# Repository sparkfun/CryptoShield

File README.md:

SparkFun CryptoShield
=====================

[*SparkFun CryptoShield (DEV-13183)*](https://www.sparkfun.com/products/13183)

Repository Contents
-------------------

* **/Hardware** - Eagle design files (.brd, .sch)
* **/Production** - Production panel files (.brd)

Documentation
--------------

* **[Hookup Guide](https://learn.sparkfun.com/tutorials/crypto-shield-hookup-guide)** - Basic hookup guide for the CryptoShield.
* **[SparkFun Fritzing repo](https://github.com/sparkfun/Fritzing_Parts)** - Fritzing diagrams for SparkFun products.
* **[SparkFun 3D Model repo](https://github.com/sparkfun/3D_Models)** - 3D models of SparkFun products. 

License Information
-------------------

This product is _**open source**_! 

Please review the LICENSE.md file for license information. 

If you have any questions or concerns on licensing, please contact techsupport@sparkfun.com.

Distributed as-is; no warranty is given.

- Your friends at SparkFun.

_A portion of each sale is given back to Josth Datko for continued development of new and exciting Cryptographic tools._

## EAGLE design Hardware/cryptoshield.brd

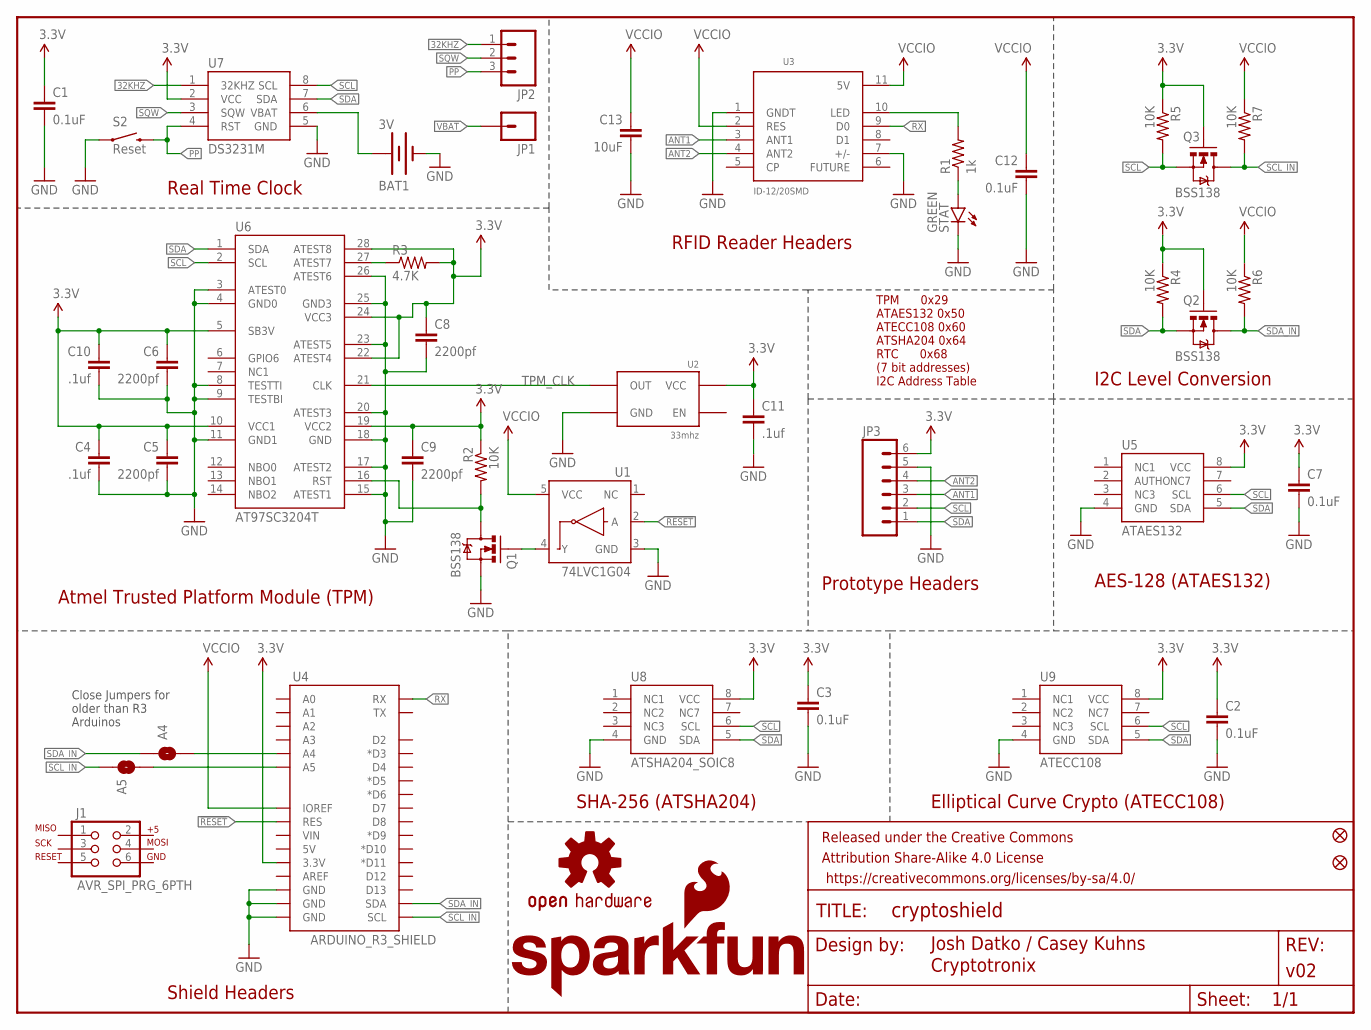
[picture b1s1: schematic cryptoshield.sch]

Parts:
A4, A5: JUMPER-PAD-2-NOYES_SILK; PAD-JUMPER-2-NO_YES_SILK
BAT1: 3V; BATTCON_12MM
C1, C2, C3, C7, C12: 0.1uF; 0603-CAP
C4, C10, C11: .1uf; 0603-CAP
C5, C6, C8, C9: 2200pf; 0603-CAP
C13: 10uF; 1210
FID1, FID2: FIDUCIAL1X2; FIDUCIAL-1X2
FRAME2: FRAME-LETTER; CREATIVE_COMMONS
J1: AVR_SPI_PRG_6PTH; 2X3
JP1: M01PTH; 1X01
JP2: M03PTH; 1X03
JP3: M06NO_SILK_FEMALE_PTH; 1X06_NO_SILK
LOGO2: OSHW-LOGOS; OSHW-LOGO-S
LOGO3: SFE_LOGO_NAME_FLAME.1_INCH; SFE_LOGO_NAME_FLAME_.1
Q1, Q2, Q3: BSS138; SOT23-3
R1: 1k; 0603-RES
R2, R4, R5, R6, R7: 10K; 0603-RES
R3: 4.7K; 0603
S2: Reset; TACTILE-SWITCH-SMD
STAT: GREEN; LED-0603
U1: 74LVC1G04; SOT353
U2: 33mhz; CRYSTAL-OSC-SMD-5X3.2
U3: ID-12/20SMD; ID-12_SMD
U4: ARDUINO_R3_SHIELD; UNO_R3_SHIELD
U5: ATAES132; SOIC8
U6: AT97SC3204T; TSSOP28
U7: DS3231M; SOIC8
U8: ATSHA204_SOIC8; SOIC8
U9: ATECC108; SOIC8

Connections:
3.3V: C1.1, C2.1, C3.1, C4.1, C5.1, C6.1, C7.1, C8.1, C9.1, C10.1, C11.1, JP3.6, Q2.1 (G), Q3.1 (G), R2.1, R3.2, R4.1, R5.1, U2.4 (VCC), U4.3.3V, U5.8 (VCC), U6.5 (SB3V), U6.10 (VCC1), U6.19 (VCC2), U6.22 (ATEST4), U6.24 (VCC3), U6.28 (ATEST8), U7.2 (VCC), U8.8 (VCC), U9.8 (VCC)
32KHZ: JP2.1, U7.1 (32KHZ)
!RESET: U1.2 (A), U4.RES
ANT1: JP3.3, U3.3 (ANT1)
ANT2: JP3.4, U3.4 (ANT2)
GND: BAT1.GND (-), C1.2, C2.2, C3.2, C4.2, C5.2, C6.2, C7.2, C8.2, C9.2, C10.2, C11.2, C12.2, C13.2, JP3.5, Q1.2 (S), S2.1, STAT.C, U1.3 (GND), U2.2 (GND), U3.1 (GNDT), U3.7 (+/-), U4.GND@0 (GND), U4.GND@1 (GND), U4.GND@2 (GND), U5.4 (GND), U6.3 (ATEST0), U6.4 (GND0), U6.8 (TESTTI), U6.9 (TESTBI), U6.11 (GND1), U6.15 (ATEST1), U6.17 (ATEST2), U6.18 (GND), U6.20 (ATEST3), U6.23 (ATEST5), U6.25 (GND3), U6.26 (ATEST6), U7.5 (GND), U8.4 (GND), U9.4 (GND)
unnamed: R1.2, U3.10 (LED)
unnamed: A4.2, U4.A4
unnamed: A5.2, U4.A5
unnamed: R1.1, STAT.A
unnamed: Q1.3 (D), R2.2, U6.16 (RST)
unnamed: R3.1, U6.27 (ATEST7)
unnamed: Q1.1 (G), U1.4 (Y)
PP: JP2.3, S2.3 (2), U7.4 (RST)
RX: U3.9 (D0), U4.RX
SCL: JP3.2, Q3.2 (S), R5.2, U5.6 (SCL), U6.2 (SCL), U7.8 (SCL), U8.6 (SCL), U9.6 (SCL)
SCL_IN: A5.1, Q3.3 (D), R7.2, U4.SCL
SDA: JP3.1, Q2.2 (S), R4.2, U5.5 (SDA), U6.1 (SDA), U7.7 (SDA), U8.5 (SDA), U9.5 (SDA)
SDA_IN: A4.1, Q2.3 (D), R6.2, U4.SDA
SQW: JP2.2, U7.3 (SQW)
TPM_CLK: U2.3 (OUT), U6.21 (CLK)
VBAT: BAT1.PWR@1 (+), JP1.1, U7.6 (VBAT)
VCCIO: C12.1, C13.1, R6.1, R7.1, U1.5 (VCC), U3.2 (RES), U3.11 (5V), U4.IOREF

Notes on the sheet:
Cryptotronix
RFID Reader Headers
I2C Level Conversion
Real Time Clock
Atmel Trusted Platform Module (TPM)
Elliptical Curve Crypto (ATECC108)
SHA-256 (ATSHA204)
Prototype Headers
I2C Address Table
TPM 0x29 ATAES132 0x50 ATECC108 0x60 ATSHA204 0x64 RTC 0x68 (7 bit addresses)
AES-128 (ATAES132)
Shield Headers
Close Jumpers for older than R3 Arduinos

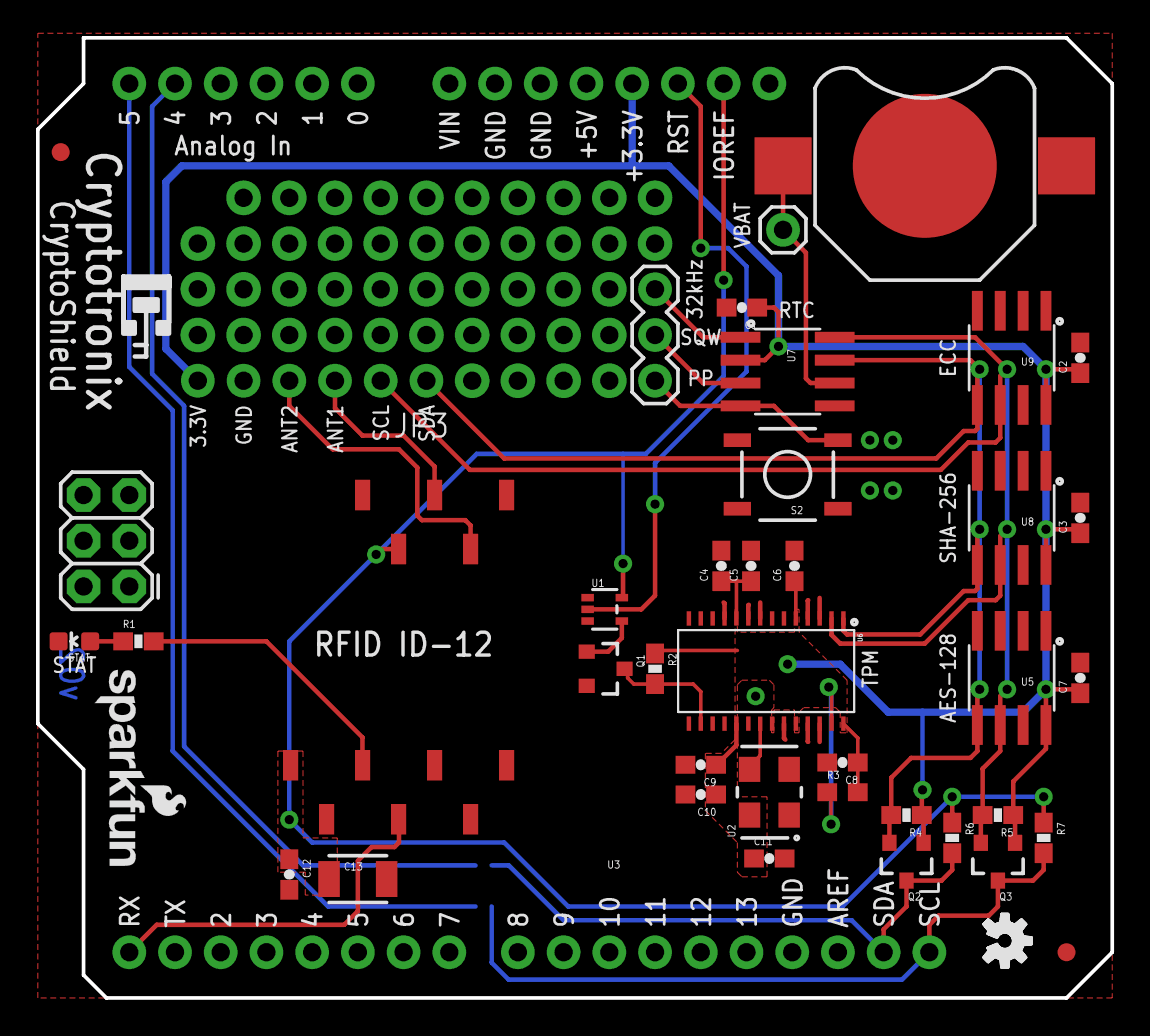
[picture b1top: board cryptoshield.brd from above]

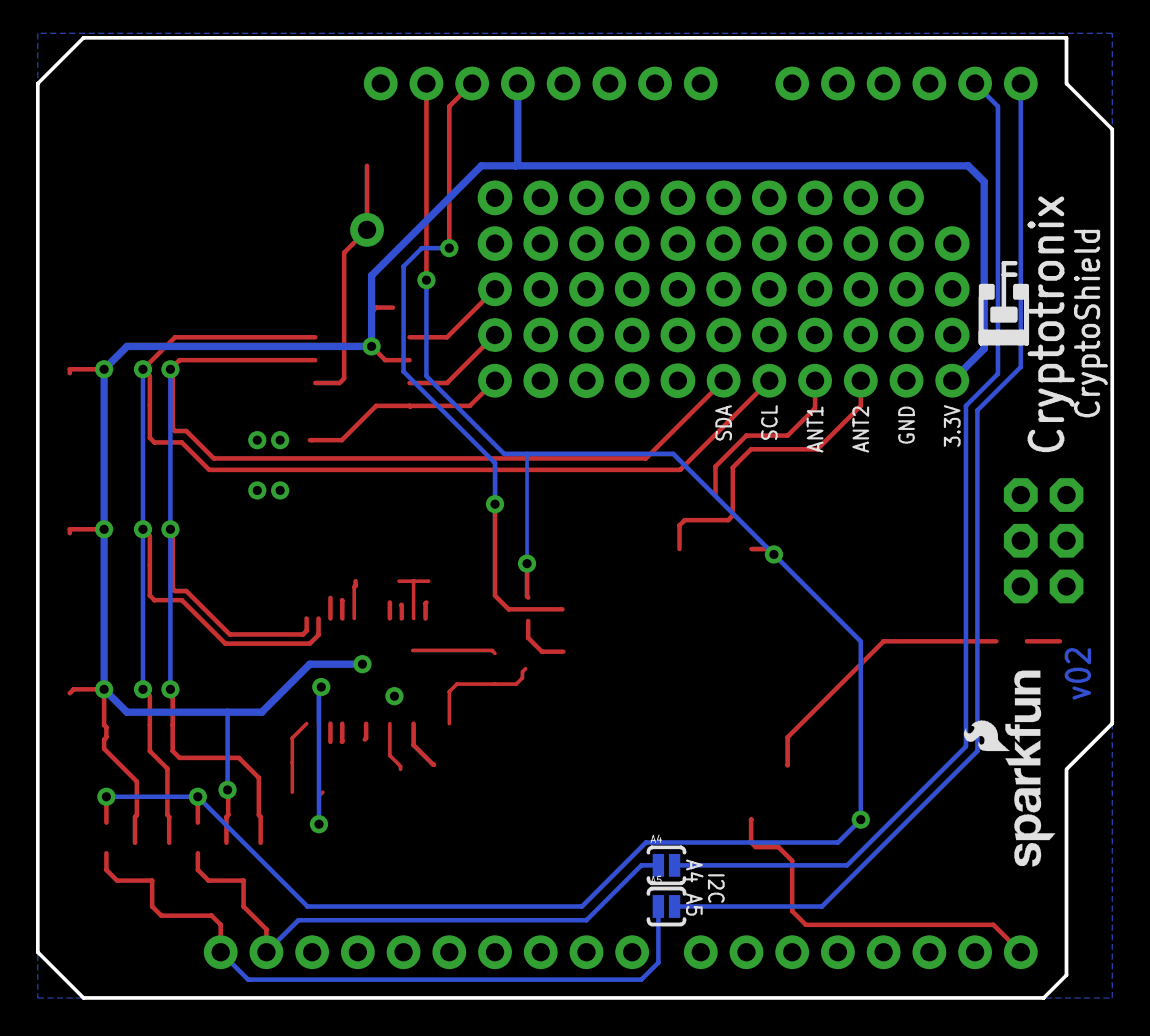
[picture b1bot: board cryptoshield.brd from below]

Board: 2 copper layers, 59.7 x 53.3 mm, 48 parts (3 on the bottom side), 23 nets.

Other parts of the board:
U$3: OSHW-LOGO-S
U$101: SFE_LOGO_NAME_FLAME_.1

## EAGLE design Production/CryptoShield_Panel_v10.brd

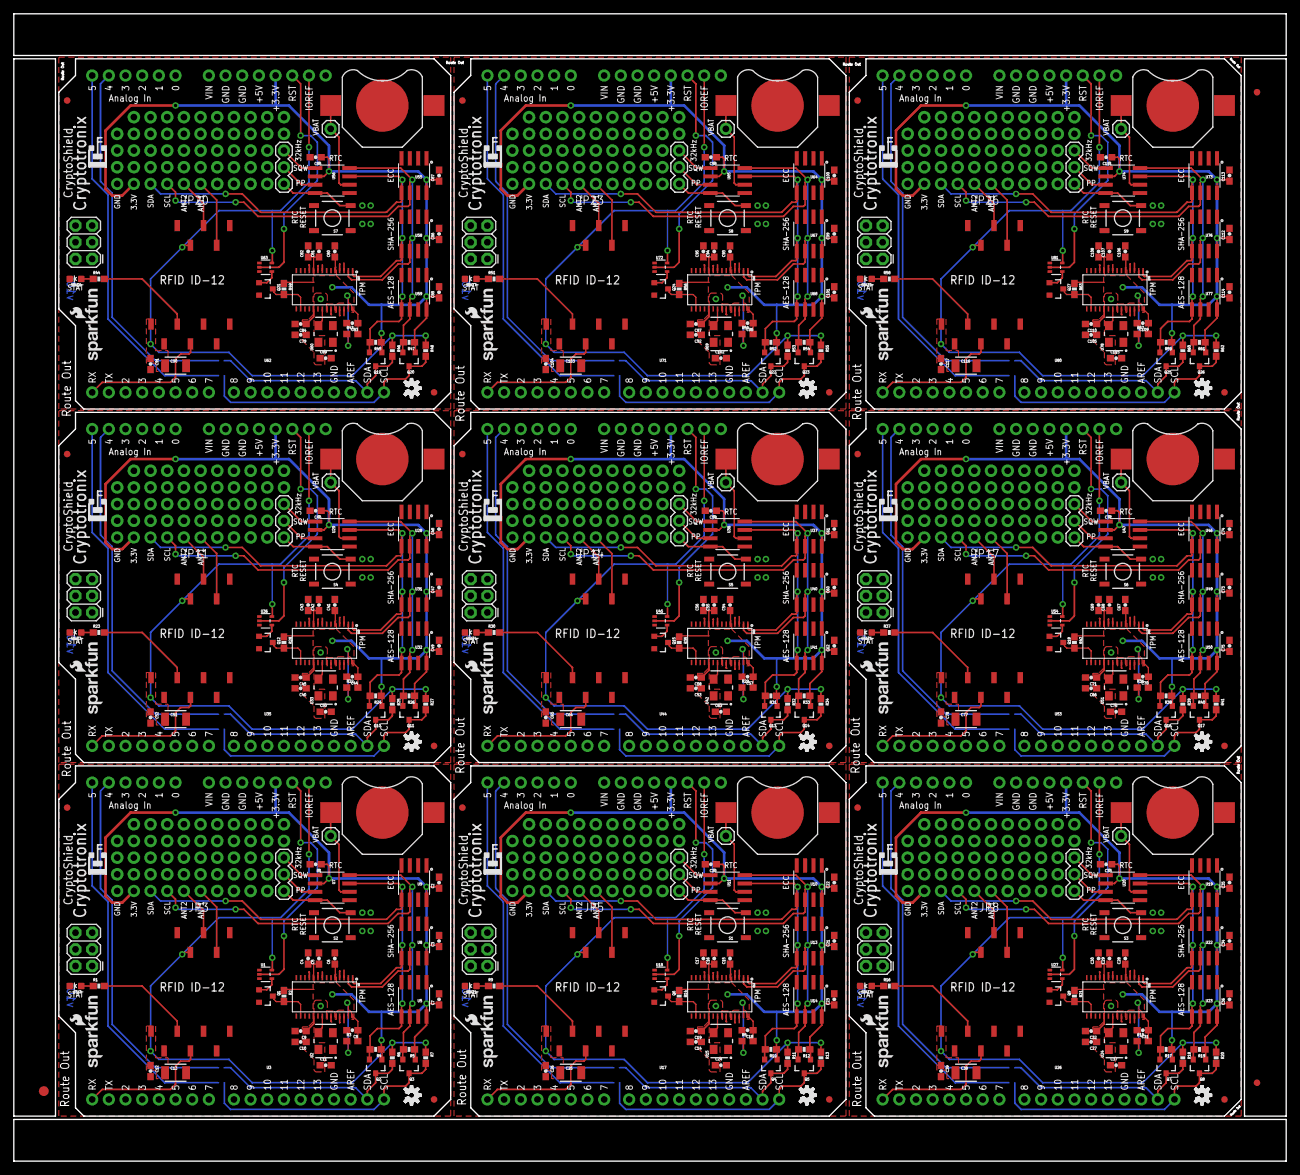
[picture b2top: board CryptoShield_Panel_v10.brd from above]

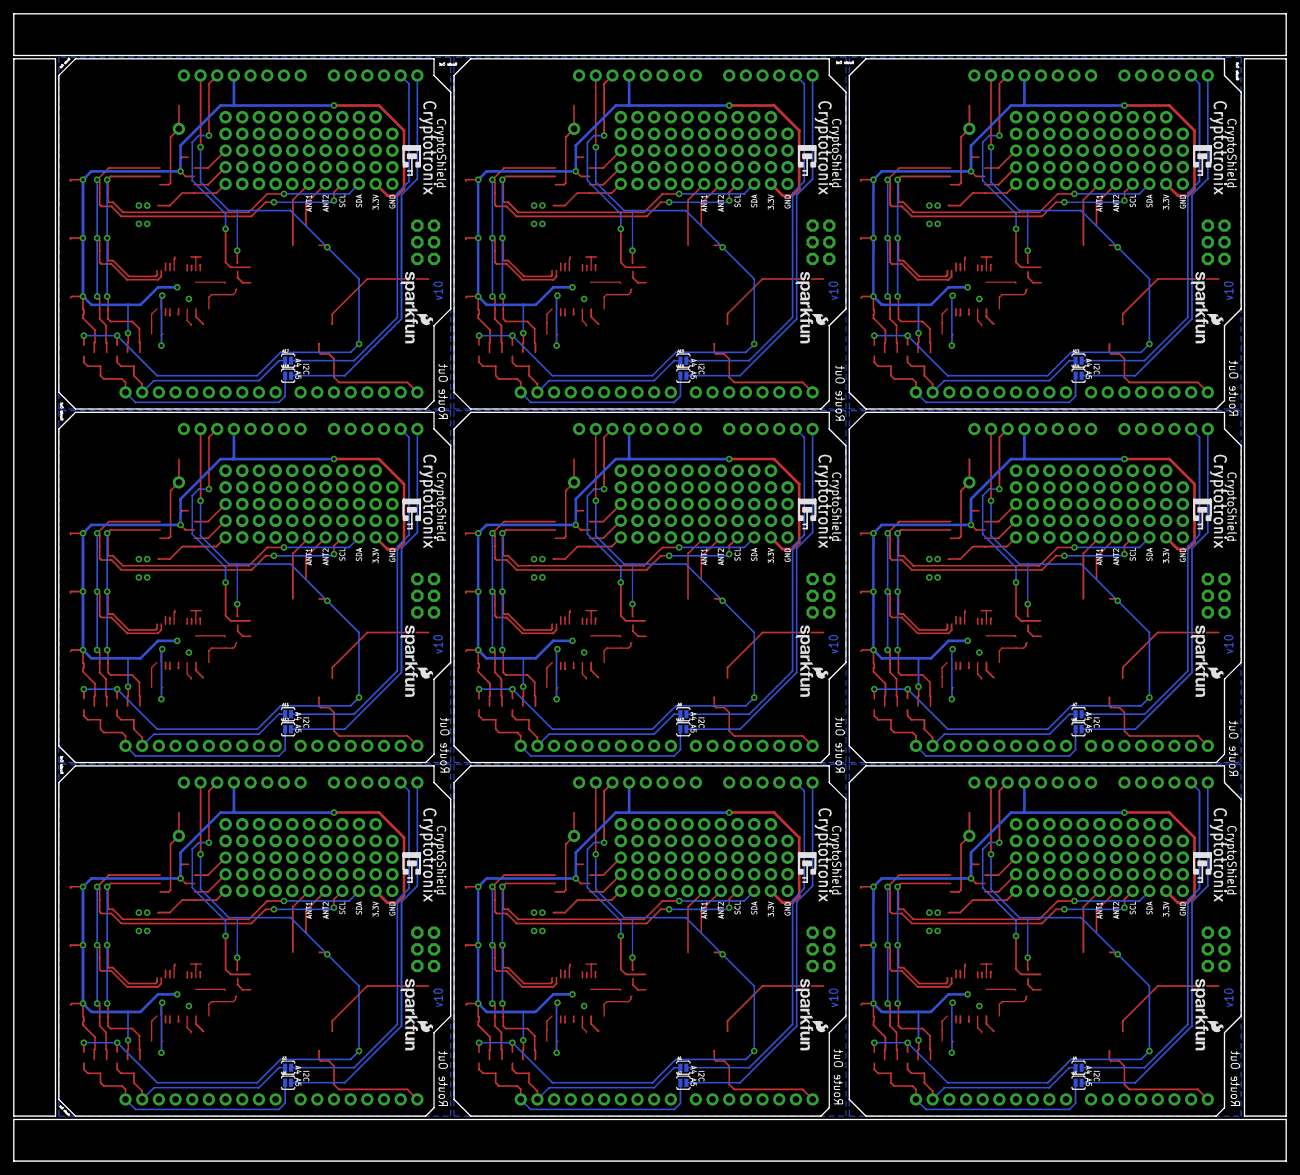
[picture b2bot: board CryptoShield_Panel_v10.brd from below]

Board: 2 copper layers, 193.8 x 174.8 mm, 426 parts (27 on the bottom side), 207 nets.

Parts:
A1, A2, A3, A4, A5, A6, A7, A8, A9, A10, A11, A12, A13, A14, A15, A16, A17, A18: PAD-JUMPER-2-NO_YES_SILK
BAT1, BAT2, BAT3, BAT4, BAT5, BAT6, BAT7, BAT8, BAT9: 3V; BATTCON_12MM
C1, C2, C3, C7, C12, C20, C21, C22, C23, C26, C33, C34, C35, C36, C39, C46, C47, C48, C49, C52, C59, C60, C61, C62, C65, C72, C73, C74, C75, C78, C85, C86, C87, C88, C91, C98, C99, C100, C101, C104, C111, C112, C113, C114, C117: 0.1uF; 0603-CAP
C4, C10, C11, C14, C17, C24, C27, C30, C37, C40, C43, C50, C53, C56, C63, C66, C69, C76, C79, C82, C89, C92, C95, C102, C105, C108, C115: .1uf; 0603-CAP
C5, C6, C8, C9, C15, C16, C18, C19, C28, C29, C31, C32, C41, C42, C44, C45, C54, C55, C57, C58, C67, C68, C70, C71, C80, C81, C83, C84, C93, C94, C96, C97, C106, C107, C109, C110: 2200pf; 0603-CAP
C13, C25, C38, C51, C64, C77, C90, C103, C116: 10uF; 1210
E$1: FIDUCIAL-1.5X3
E$6, E$8: FIDUCIAL-1X2
FID1, FID2, FID3, FID4, FID5, FID6, FID7, FID8, FID9, FID10, FID11, FID12, FID13, FID14, FID15, FID16, FID17, FID18: FIDUCIAL1X2; FIDUCIAL-1X2
J1, J2, J3, J4, J5, J6, J7, J8, J9: AVR_SPI_PRG_6PTH; 2X3
JP1, JP4, JP7, JP10, JP13, JP16, JP19, JP22, JP25: M01PTH; 1X01
JP2, JP6, JP9, JP12, JP15, JP18, JP21, JP24, JP27: 1X03
JP3, JP5, JP8, JP11, JP14, JP17, JP20, JP23, JP26: 1X06_NO_SILK
LOGO1, LOGO2, LOGO5, LOGO7, LOGO9, LOGO11, LOGO13, LOGO15, LOGO17: OSHW-LOGOS; OSHW-LOGO-S
LOGO3, LOGO4, LOGO6, LOGO8, LOGO10, LOGO12, LOGO14, LOGO16, LOGO18: SFE_LOGO_NAME_FLAME.1_INCH; SFE_LOGO_NAME_FLAME_.1
Q1, Q2, Q3, Q4, Q5, Q6, Q7, Q8, Q9, Q10, Q11, Q12, Q13, Q14, Q15, Q16, Q17, Q18, Q19, Q20, Q21, Q22, Q23, Q24, Q25, Q26, Q27: BSS138; SOT23-3
R1, R9, R16, R23, R30, R37, R44, R51, R58: 1k; 0603-RES
R2, R4, R5, R6, R7, R10, R11, R12, R13, R14, R17, R18, R19, R20, R21, R24, R25, R26, R27, R28, R31, R32, R33, R34, R35, R38, R39, R40, R41, R42, R45, R46, R47, R48, R49, R52, R53, R54, R55, R56, R59, R60, R61, R62, R63: 10K; 0603-RES
R3, R8, R15, R22, R29, R36, R43, R50, R57: 4.7K; 0603
S1, S2, S3, S4, S5, S6, S7, S8, S9: Reset; TACTILE-SWITCH-SMD
STAT, STAT1, STAT2, STAT3, STAT4, STAT5, STAT6, STAT7, STAT8: GREEN; LED-0603
U1, U18, U27, U36, U45, U54, U63, U72, U81: 74LVC1G04; SOT353
U2, U15, U24, U33, U42, U51, U60, U69, U78: 33mhz; CRYSTAL-OSC-SMD-5X3.2
U3, U17, U26, U35, U44, U53, U62, U71, U80: ID-12/20SMD; ID-12_SMD
U4, U16, U25, U34, U43, U52, U61, U70, U79: ARDUINO_R3_SHIELD; UNO_R3_SHIELD
U5, U14, U23, U32, U41, U50, U59, U68, U77: ATAES132; SOIC8
U6, U12, U21, U30, U39, U48, U57, U66, U75: AT97SC3204T; TSSOP28
U7, U11, U20, U29, U38, U47, U56, U65, U74: DS3231M; SOIC8
U8, U13, U22, U31, U40, U49, U58, U67, U76: ATSHA204_SOIC8; SOIC8
U9, U10, U19, U28, U37, U46, U55, U64, U73: ATECC108; SOIC8
U$1, U$3, U$4, U$6, U$8, U$10, U$12, U$14, U$16: OSHW-LOGO-S
U$2, U$5, U$7, U$9, U$11, U$13, U$15, U$17, U$101: SFE_LOGO_NAME_FLAME_.1

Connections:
3.3V: C1.1, C2.1, C3.1, C4.1, C5.1, C6.1, C7.1, C8.1, C9.1, C10.1, C11.1, JP3.5, Q2.1, Q3.1, R2.1, R3.2, R4.1, R5.1, U2.4, U4.3.3V, U5.8, U6.5, U6.10, U6.19, U6.22, U6.24, U6.28, U7.2, U8.8, U9.8
3.3V1: C14.1, C15.1, C16.1, C17.1, C18.1, C19.1, C20.1, C21.1, C22.1, C23.1, C24.1, JP5.5, Q4.1, Q5.1, R8.2, R10.1, R12.1, R14.1, U10.8, U11.2, U12.5, U12.10, U12.19, U12.22, U12.24, U12.28, U13.8, U14.8, U15.4, U16.3.3V
3.3V2: C27.1, C28.1, C29.1, C30.1, C31.1, C32.1, C33.1, C34.1, C35.1, C36.1, C37.1, JP8.5, Q7.1, Q8.1, R15.2, R17.1, R19.1, R21.1, U19.8, U20.2, U21.5, U21.10, U21.19, U21.22, U21.24, U21.28, U22.8, U23.8, U24.4, U25.3.3V
3.3V3: C40.1, C41.1, C42.1, C43.1, C44.1, C45.1, C46.1, C47.1, C48.1, C49.1, C50.1, JP11.5, Q10.1, Q11.1, R22.2, R24.1, R26.1, R28.1, U28.8, U29.2, U30.5, U30.10, U30.19, U30.22, U30.24, U30.28, U31.8, U32.8, U33.4, U34.3.3V
3.3V4: C53.1, C54.1, C55.1, C56.1, C57.1, C58.1, C59.1, C60.1, C61.1, C62.1, C63.1, JP14.5, Q13.1, Q14.1, R29.2, R31.1, R33.1, R35.1, U37.8, U38.2, U39.5, U39.10, U39.19, U39.22, U39.24, U39.28, U40.8, U41.8, U42.4, U43.3.3V
3.3V5: C66.1, C67.1, C68.1, C69.1, C70.1, C71.1, C72.1, C73.1, C74.1, C75.1, C76.1, JP17.5, Q16.1, Q17.1, R36.2, R38.1, R40.1, R42.1, U46.8, U47.2, U48.5, U48.10, U48.19, U48.22, U48.24, U48.28, U49.8, U50.8, U51.4, U52.3.3V
3.3V6: C79.1, C80.1, C81.1, C82.1, C83.1, C84.1, C85.1, C86.1, C87.1, C88.1, C89.1, JP20.5, Q19.1, Q20.1, R43.2, R45.1, R47.1, R49.1, U55.8, U56.2, U57.5, U57.10, U57.19, U57.22, U57.24, U57.28, U58.8, U59.8, U60.4, U61.3.3V
3.3V7: C92.1, C93.1, C94.1, C95.1, C96.1, C97.1, C98.1, C99.1, C100.1, C101.1, C102.1, JP23.5, Q22.1, Q23.1, R50.2, R52.1, R54.1, R56.1, U64.8, U65.2, U66.5, U66.10, U66.19, U66.22, U66.24, U66.28, U67.8, U68.8, U69.4, U70.3.3V
3.3V8: C105.1, C106.1, C107.1, C108.1, C109.1, C110.1, C111.1, C112.1, C113.1, C114.1, C115.1, JP26.5, Q25.1, Q26.1, R57.2, R59.1, R61.1, R63.1, U73.8, U74.2, U75.5, U75.10, U75.19, U75.22, U75.24, U75.28, U76.8, U77.8, U78.4, U79.3.3V
32KHZ: JP2.1, U7.1
32KHZ1: JP6.1, U11.1
32KHZ2: JP9.1, U20.1
32KHZ3: JP12.1, U29.1
32KHZ4: JP15.1, U38.1
32KHZ5: JP18.1, U47.1
32KHZ6: JP21.1, U56.1
32KHZ7: JP24.1, U65.1
32KHZ8: JP27.1, U74.1
!RESET: U1.2, U4.RES
!RESET1: U16.RES, U18.2
!RESET2: U25.RES, U27.2
!RESET3: U34.RES, U36.2
!RESET4: U43.RES, U45.2
!RESET5: U52.RES, U54.2
!RESET6: U61.RES, U63.2
!RESET7: U70.RES, U72.2
!RESET8: U79.RES, U81.2
ANT1: JP3.2, U3.3
ANT2: JP3.1, U3.4
ANT3: JP5.2, U17.3
ANT4: JP5.1, U17.4
ANT5: JP8.2, U26.3
ANT6: JP8.1, U26.4
ANT7: JP11.2, U35.3
ANT8: JP11.1, U35.4
ANT9: JP14.2, U44.3
ANT10: JP14.1, U44.4
ANT11: JP17.2, U53.3
ANT12: JP17.1, U53.4
ANT13: JP20.2, U62.3
ANT14: JP20.1, U62.4
ANT15: JP23.2, U71.3
ANT16: JP23.1, U71.4
ANT17: JP26.2, U80.3
ANT18: JP26.1, U80.4
GND: BAT1.GND, C1.2, C2.2, C3.2, C4.2, C5.2, C6.2, C7.2, C8.2, C9.2, C10.2, C11.2, C12.2, C13.2, JP3.6, Q1.2, S2.1, STAT.C, U1.3, U2.2, U3.1, U3.7, U4.GND@0, U4.GND@1, U4.GND@2, U5.4, U6.3, U6.4, U6.8, U6.9, U6.11, U6.15, U6.17, U6.18, U6.20, U6.23, U6.25, U6.26, U7.5, U8.4, U9.4
GND1: BAT2.GND, C14.2, C15.2, C16.2, C17.2, C18.2, C19.2, C20.2, C21.2, C22.2, C23.2, C24.2, C25.2, C26.2, JP5.6, Q6.2, S1.1, STAT1.C, U10.4, U11.5, U12.3, U12.4, U12.8, U12.9, U12.11, U12.15, U12.17, U12.18, U12.20, U12.23, U12.25, U12.26, U13.4, U14.4, U15.2, U16.GND@0, U16.GND@1, U16.GND@2, U17.1, U17.7, U18.3
GND2: BAT3.GND, C27.2, C28.2, C29.2, C30.2, C31.2, C32.2, C33.2, C34.2, C35.2, C36.2, C37.2, C38.2, C39.2, JP8.6, Q9.2, S3.1, STAT2.C, U19.4, U20.5, U21.3, U21.4, U21.8, U21.9, U21.11, U21.15, U21.17, U21.18, U21.20, U21.23, U21.25, U21.26, U22.4, U23.4, U24.2, U25.GND@0, U25.GND@1, U25.GND@2, U26.1, U26.7, U27.3
GND3: BAT4.GND, C40.2, C41.2, C42.2, C43.2, C44.2, C45.2, C46.2, C47.2, C48.2, C49.2, C50.2, C51.2, C52.2, JP11.6, Q12.2, S4.1, STAT3.C, U28.4, U29.5, U30.3, U30.4, U30.8, U30.9, U30.11, U30.15, U30.17, U30.18, U30.20, U30.23, U30.25, U30.26, U31.4, U32.4, U33.2, U34.GND@0, U34.GND@1, U34.GND@2, U35.1, U35.7, U36.3
GND4: BAT5.GND, C53.2, C54.2, C55.2, C56.2, C57.2, C58.2, C59.2, C60.2, C61.2, C62.2, C63.2, C64.2, C65.2, JP14.6, Q15.2, S5.1, STAT4.C, U37.4, U38.5, U39.3, U39.4, U39.8, U39.9, U39.11, U39.15, U39.17, U39.18, U39.20, U39.23, U39.25, U39.26, U40.4, U41.4, U42.2, U43.GND@0, U43.GND@1, U43.GND@2, U44.1, U44.7, U45.3
GND5: BAT6.GND, C66.2, C67.2, C68.2, C69.2, C70.2, C71.2, C72.2, C73.2, C74.2, C75.2, C76.2, C77.2, C78.2, JP17.6, Q18.2, S6.1, STAT5.C, U46.4, U47.5, U48.3, U48.4, U48.8, U48.9, U48.11, U48.15, U48.17, U48.18, U48.20, U48.23, U48.25, U48.26, U49.4, U50.4, U51.2, U52.GND@0, U52.GND@1, U52.GND@2, U53.1, U53.7, U54.3
GND6: BAT7.GND, C79.2, C80.2, C81.2, C82.2, C83.2, C84.2, C85.2, C86.2, C87.2, C88.2, C89.2, C90.2, C91.2, JP20.6, Q21.2, S7.1, STAT6.C, U55.4, U56.5, U57.3, U57.4, U57.8, U57.9, U57.11, U57.15, U57.17, U57.18, U57.20, U57.23, U57.25, U57.26, U58.4, U59.4, U60.2, U61.GND@0, U61.GND@1, U61.GND@2, U62.1, U62.7, U63.3
GND7: BAT8.GND, C92.2, C93.2, C94.2, C95.2, C96.2, C97.2, C98.2, C99.2, C100.2, C101.2, C102.2, C103.2, C104.2, JP23.6, Q24.2, S8.1, STAT7.C, U64.4, U65.5, U66.3, U66.4, U66.8, U66.9, U66.11, U66.15, U66.17, U66.18, U66.20, U66.23, U66.25, U66.26, U67.4, U68.4, U69.2, U70.GND@0, U70.GND@1, U70.GND@2, U71.1, U71.7, U72.3
GND8: BAT9.GND, C105.2, C106.2, C107.2, C108.2, C109.2, C110.2, C111.2, C112.2, C113.2, C114.2, C115.2, C116.2, C117.2, JP26.6, Q27.2, S9.1, STAT8.C, U73.4, U74.5, U75.3, U75.4, U75.8, U75.9, U75.11, U75.15, U75.17, U75.18, U75.20, U75.23, U75.25, U75.26, U76.4, U77.4, U78.2, U79.GND@0, U79.GND@1, U79.GND@2, U80.1, U80.7, U81.3
unnamed: R1.2, U3.10
unnamed: A4.2, U4.A4
unnamed: A5.2, U4.A5
unnamed: R1.1, STAT.A
unnamed: Q1.3, R2.2, U6.16
unnamed: R3.1, U6.27
unnamed: Q1.1, U1.4
unnamed: R8.1, U12.27
unnamed: R9.1, STAT1.A
unnamed: R9.2, U17.10
unnamed: A1.2, U16.A4
unnamed: A2.2, U16.A5
unnamed: Q6.3, R14.2, U12.16
unnamed: Q6.1, U18.4
unnamed: R15.1, U21.27
unnamed: R16.1, STAT2.A
unnamed: R16.2, U26.10
unnamed: A3.2, U25.A4
unnamed: A6.2, U25.A5
unnamed: Q9.3, R21.2, U21.16
unnamed: Q9.1, U27.4
unnamed: R22.1, U30.27
unnamed: R23.1, STAT3.A
unnamed: R23.2, U35.10
unnamed: A7.2, U34.A4
unnamed: A8.2, U34.A5
unnamed: Q12.3, R28.2, U30.16
unnamed: Q12.1, U36.4
unnamed: R29.1, U39.27
unnamed: R30.1, STAT4.A
unnamed: R30.2, U44.10
unnamed: A9.2, U43.A4
unnamed: A10.2, U43.A5
unnamed: Q15.3, R35.2, U39.16
unnamed: Q15.1, U45.4
unnamed: R36.1, U48.27
unnamed: R37.1, STAT5.A
unnamed: R37.2, U53.10
unnamed: A11.2, U52.A4
unnamed: A12.2, U52.A5
unnamed: Q18.3, R42.2, U48.16
unnamed: Q18.1, U54.4
unnamed: R43.1, U57.27
unnamed: R44.1, STAT6.A
unnamed: R44.2, U62.10
unnamed: A13.2, U61.A4
unnamed: A14.2, U61.A5
unnamed: Q21.3, R49.2, U57.16
unnamed: Q21.1, U63.4
unnamed: R50.1, U66.27
unnamed: R51.1, STAT7.A
unnamed: R51.2, U71.10
unnamed: A15.2, U70.A4
unnamed: A16.2, U70.A5
unnamed: Q24.3, R56.2, U66.16
unnamed: Q24.1, U72.4
unnamed: R57.1, U75.27
unnamed: R58.1, STAT8.A
unnamed: R58.2, U80.10
unnamed: A17.2, U79.A4
unnamed: A18.2, U79.A5
unnamed: Q27.3, R63.2, U75.16
unnamed: Q27.1, U81.4
PP: JP2.3, S2.3, U7.4
PP1: JP6.3, S1.3, U11.4
PP2: JP9.3, S3.3, U20.4
PP3: JP12.3, S4.3, U29.4
PP4: JP15.3, S5.3, U38.4
PP5: JP18.3, S6.3, U47.4
PP6: JP21.3, S7.3, U56.4
PP7: JP24.3, S8.3, U65.4
PP8: JP27.3, S9.3, U74.4
RX: U3.9, U4.RX
RX1: U16.RX, U17.9
RX2: U25.RX, U26.9
RX3: U34.RX, U35.9
RX4: U43.RX, U44.9
RX5: U52.RX, U53.9
RX6: U61.RX, U62.9
RX7: U70.RX, U71.9
RX8: U79.RX, U80.9
SCL: JP3.3, Q3.2, R5.2, U5.6, U6.2, U7.8, U8.6, U9.6
SCL1: JP5.3, Q5.2, R12.2, U10.6, U11.8, U12.2, U13.6, U14.6
SCL2: JP8.3, Q8.2, R19.2, U19.6, U20.8, U21.2, U22.6, U23.6
SCL3: JP11.3, Q11.2, R26.2, U28.6, U29.8, U30.2, U31.6, U32.6
SCL4: JP14.3, Q14.2, R33.2, U37.6, U38.8, U39.2, U40.6, U41.6
SCL5: JP17.3, Q17.2, R40.2, U46.6, U47.8, U48.2, U49.6, U50.6
SCL6: JP20.3, Q20.2, R47.2, U55.6, U56.8, U57.2, U58.6, U59.6
SCL7: JP23.3, Q23.2, R54.2, U64.6, U65.8, U66.2, U67.6, U68.6
SCL8: JP26.3, Q26.2, R61.2, U73.6, U74.8, U75.2, U76.6, U77.6
SCL_IN: A5.1, Q3.3, R7.2, U4.SCL
SCL_IN1: A2.1, Q5.3, R13.2, U16.SCL
SCL_IN2: A6.1, Q8.3, R20.2, U25.SCL
SCL_IN3: A8.1, Q11.3, R27.2, U34.SCL
SCL_IN4: A10.1, Q14.3, R34.2, U43.SCL
SCL_IN5: A12.1, Q17.3, R41.2, U52.SCL
SCL_IN6: A14.1, Q20.3, R48.2, U61.SCL
SCL_IN7: A16.1, Q23.3, R55.2, U70.SCL
SCL_IN8: A18.1, Q26.3, R62.2, U79.SCL
SDA: JP3.4, Q2.2, R4.2, U5.5, U6.1, U7.7, U8.5, U9.5
SDA1: JP5.4, Q4.2, R10.2, U10.5, U11.7, U12.1, U13.5, U14.5
SDA2: JP8.4, Q7.2, R17.2, U19.5, U20.7, U21.1, U22.5, U23.5
SDA3: JP11.4, Q10.2, R24.2, U28.5, U29.7, U30.1, U31.5, U32.5
SDA4: JP14.4, Q13.2, R31.2, U37.5, U38.7, U39.1, U40.5, U41.5
SDA5: JP17.4, Q16.2, R38.2, U46.5, U47.7, U48.1, U49.5, U50.5
SDA6: JP20.4, Q19.2, R45.2, U55.5, U56.7, U57.1, U58.5, U59.5
SDA7: JP23.4, Q22.2, R52.2, U64.5, U65.7, U66.1, U67.5, U68.5
SDA8: JP26.4, Q25.2, R59.2, U73.5, U74.7, U75.1, U76.5, U77.5
SDA_IN: A4.1, Q2.3, R6.2, U4.SDA
SDA_IN1: A1.1, Q4.3, R11.2, U16.SDA
SDA_IN2: A3.1, Q7.3, R18.2, U25.SDA
SDA_IN3: A7.1, Q10.3, R25.2, U34.SDA
SDA_IN4: A9.1, Q13.3, R32.2, U43.SDA
SDA_IN5: A11.1, Q16.3, R39.2, U52.SDA
SDA_IN6: A13.1, Q19.3, R46.2, U61.SDA
SDA_IN7: A15.1, Q22.3, R53.2, U70.SDA
SDA_IN8: A17.1, Q25.3, R60.2, U79.SDA
SQW: JP2.2, U7.3
SQW1: JP6.2, U11.3
SQW2: JP9.2, U20.3
SQW3: JP12.2, U29.3
SQW4: JP15.2, U38.3
SQW5: JP18.2, U47.3
SQW6: JP21.2, U56.3
SQW7: JP24.2, U65.3
SQW8: JP27.2, U74.3
TPM_CLK: U2.3, U6.21
TPM_CLK1: U12.21, U15.3
TPM_CLK2: U21.21, U24.3
TPM_CLK3: U30.21, U33.3
TPM_CLK4: U39.21, U42.3
TPM_CLK5: U48.21, U51.3
TPM_CLK6: U57.21, U60.3
TPM_CLK7: U66.21, U69.3
TPM_CLK8: U75.21, U78.3
VBAT: BAT1.PWR@1, JP1.1, U7.6
VBAT1: BAT2.PWR@1, JP4.1, U11.6
VBAT2: BAT3.PWR@1, JP7.1, U20.6
VBAT3: BAT4.PWR@1, JP10.1, U29.6
VBAT4: BAT5.PWR@1, JP13.1, U38.6
VBAT5: BAT6.PWR@1, JP16.1, U47.6
VBAT6: BAT7.PWR@1, JP19.1, U56.6
VBAT7: BAT8.PWR@1, JP22.1, U65.6
VBAT8: BAT9.PWR@1, JP25.1, U74.6
VCCIO: C12.1, C13.1, R6.1, R7.1, U1.5, U3.2, U3.11, U4.IOREF
VCCIO1: C25.1, C26.1, R11.1, R13.1, U16.IOREF, U17.2, U17.11, U18.5
VCCIO2: C38.1, C39.1, R18.1, R20.1, U25.IOREF, U26.2, U26.11, U27.5
VCCIO3: C51.1, C52.1, R25.1, R27.1, U34.IOREF, U35.2, U35.11, U36.5
VCCIO4: C64.1, C65.1, R32.1, R34.1, U43.IOREF, U44.2, U44.11, U45.5
VCCIO5: C77.1, C78.1, R39.1, R41.1, U52.IOREF, U53.2, U53.11, U54.5
VCCIO6: C90.1, C91.1, R46.1, R48.1, U61.IOREF, U62.2, U62.11, U63.5
VCCIO7: C103.1, C104.1, R53.1, R55.1, U70.IOREF, U71.2, U71.11, U72.5
VCCIO8: C116.1, C117.1, R60.1, R62.1, U79.IOREF, U80.2, U80.11, U81.5

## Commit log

2014-10-08 initial commit, Work in progress
2014-10-09 more work done, still work in progress
2014-10-09 finished layout, ready for review
2014-10-15 fixed silk
2014-10-15 fixed wire
2014-10-21 fixed silk added gitignore
2014-10-21 changed name of part
2014-11-06 Changes 5V to IOREF
2014-12-09 added mosfet reset circuit to couple TPM reset to Arduino Reset pin
2015-01-08 made changed to isolate Reset from 5V
2015-01-09 modified layout to meet checklist compliance
2015-01-12 fixed all github issues
2015-01-12 fixed fonts
2015-02-02 Moved Stat Led away from board re-arranged proto area to conform with I2C standard layout flipped logos to match lable orientation
2015-02-04 created panel v10
2015-10-27 Updating product repo structure, readme with product info

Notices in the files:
parts and their libraries:
SparkFun-Passives: Licensing: CC v3.0 Share-Alike You are welcome to use this library for commercial purposes.
SparkFun-Aesthetics: Released under the Creative Commons Attribution Share-Alike 4.0 License
SparkFun-Aesthetics: https://creativecommons.org/licenses/by-sa/4.0
